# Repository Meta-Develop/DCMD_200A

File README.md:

# DCMD_200A

This repository is about the motor-driver for driving DC-brush motors on robots.

## License

This hardware design is licensed under [CERN-OHL-S-2.0](LICENSE). See [NOTICE](NOTICE) for attribution and third-party exceptions.

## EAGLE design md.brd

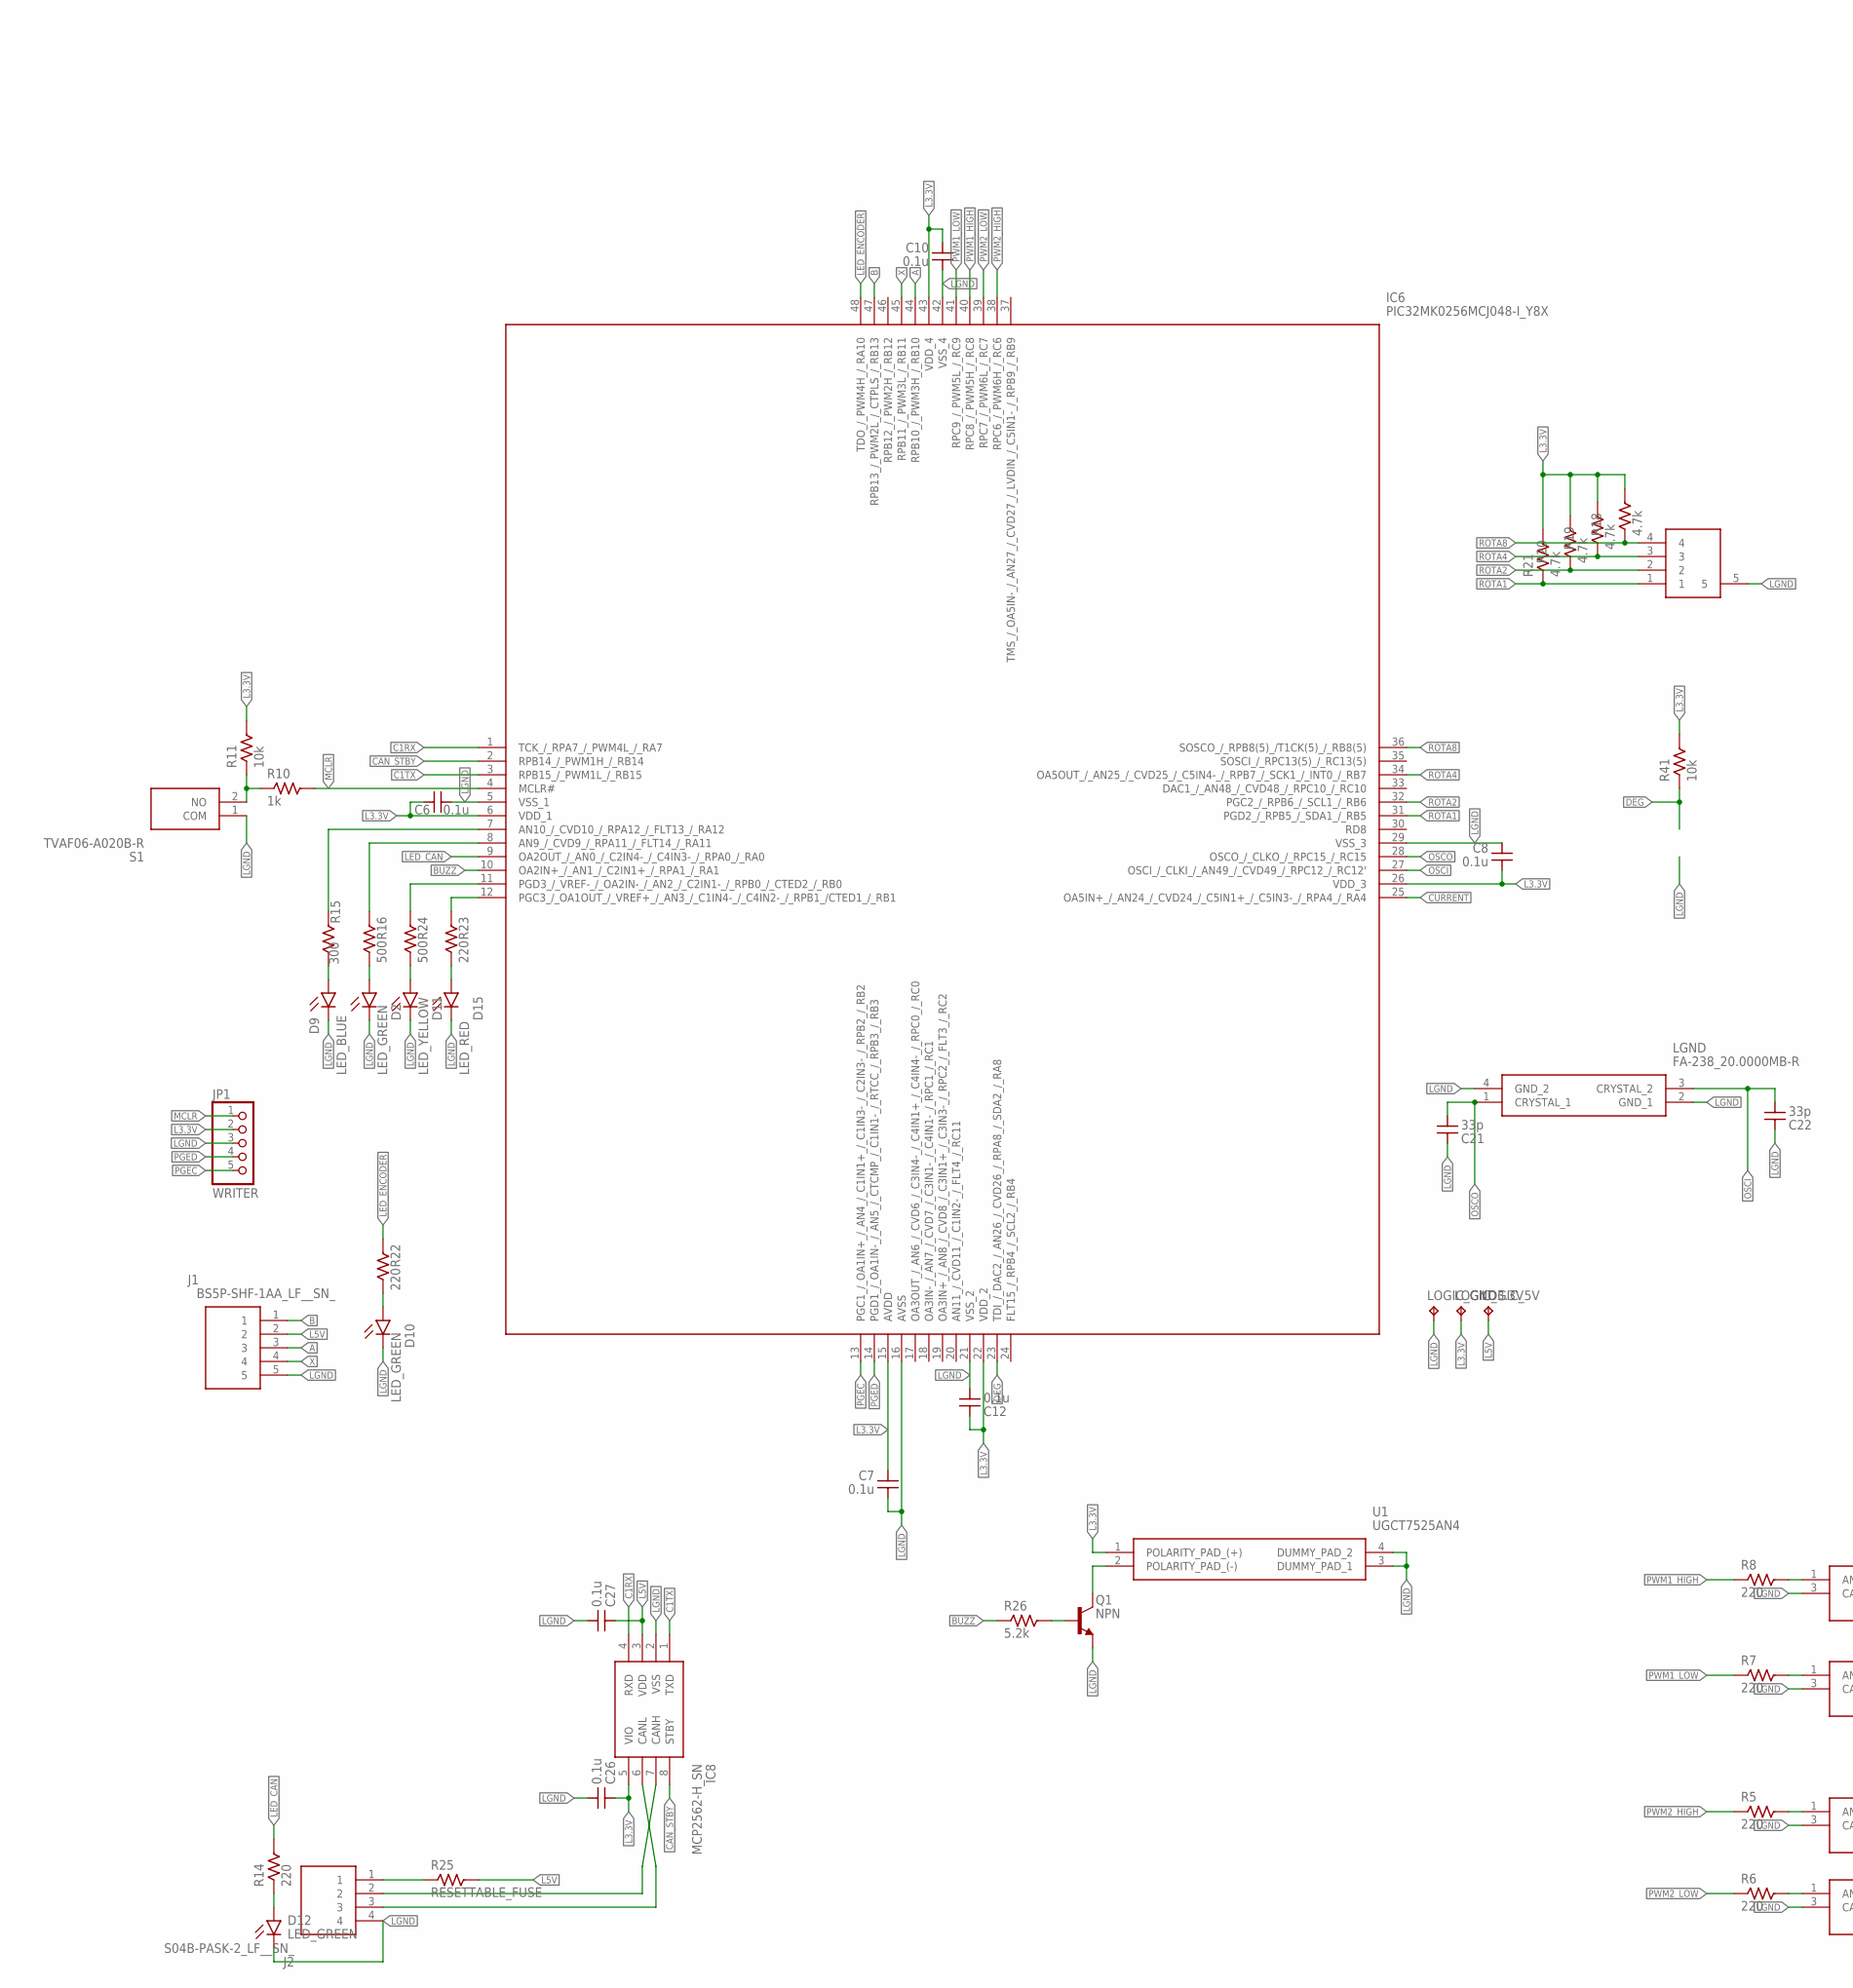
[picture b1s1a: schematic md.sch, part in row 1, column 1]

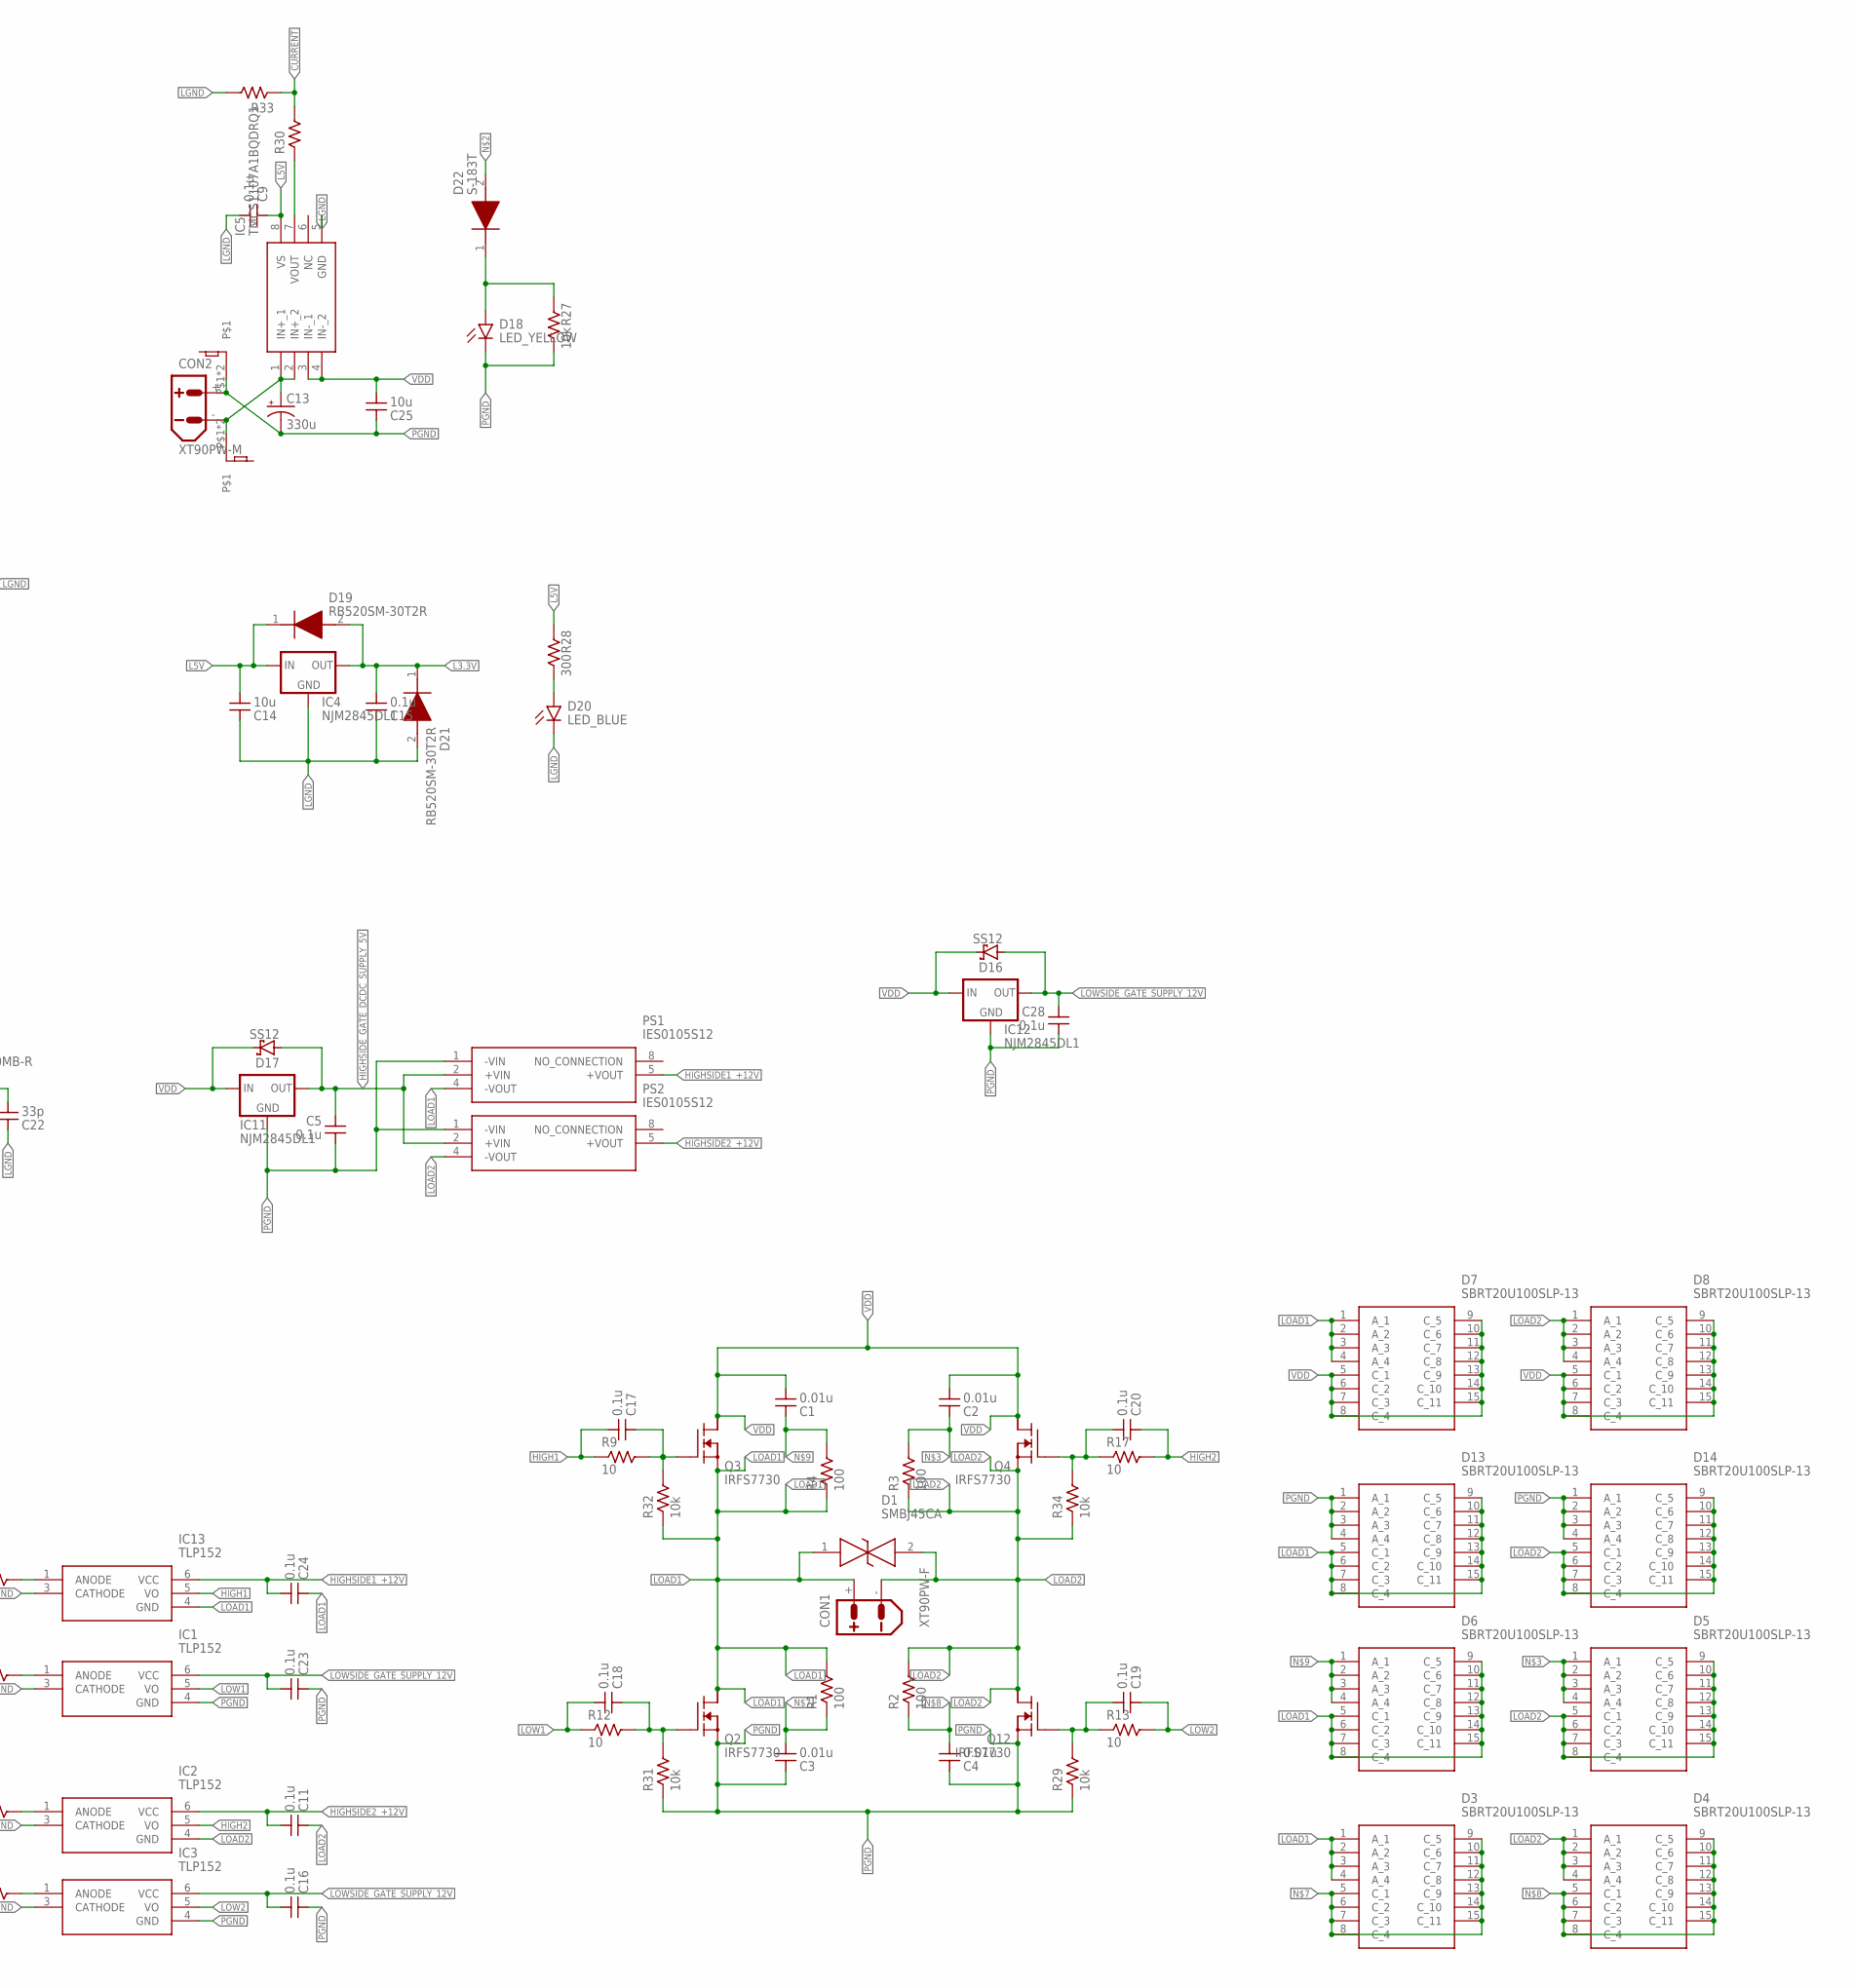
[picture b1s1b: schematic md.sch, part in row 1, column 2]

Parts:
C1, C2, C3, C4: 0.01u; C3216
C5, C6, C7, C8, C9, C10, C11, C12, C15, C16, C17, C18, C19, C20, C23, C24, C26, C27, C28: 0.1u; C1608
C13: 330u; CAPAE830X1050N
C14: 10u; C1608
C21, C22: 33p; C1608
C25: 10u; C3216
CON1: XT90PW-F
CON2: XT90PW-M
D1: SMBJ45CA; DIOM5336X265N
D2, D10, D12: LED_GREEN; LEDC1608X55N_FLAT-G
D3, D4, D5, D6, D7, D8, D13, D14: SBRT20U100SLP-13; SBRT20U100SLP13
D9, D20: LED_BLUE; LEDC1608X55N_FLAT-B
D11, D18: LED_YELLOW; LEDC1608X55N_FLAT-Y
D15: LED_RED; LEDC1608X55N_FLAT-R
D16, D17: SS12; SMA
D19, D21: RB520SM-30T2R; DIOC1608X70N
D22: S-183T; SODFL3516X70N
IC1, IC2, IC3, IC13: TLP152; 11-4L1S(5-PIN-SOIC)
IC4, IC11, IC12: NJM2845DL1; TO252
IC5: TMCS1107A1BQDRQ1; SOIC127P600X175-8N
IC6: PIC32MK0256MCJ048-I_Y8X; QFP50P900X900X120-48N
IC8: MCP2562-H_SN; SOIC127P600X175-8N
J1: BS5P-SHF-1AA_LF__SN_; HDRRA5W64P0X250_1X5_1250X600X5
J2: S04B-PASK-2_LF__SN_; S04BPASK2LFSN
JP1: WRITER; 1X05/90
LGND: FA-238_20.0000MB-R; FA238200000MBR
LOGIC_3.3V, LOGIC_5V: TPPAD1-13; P1-13
LOGIC_GND: TPPAD1-13; P1-13
PS1, PS2: IES0105S12
Q1: NPN; SC59
Q2, Q3, Q4, Q12: IRFS7730; D2PAK-7
R1, R2, R3, R4: 100; C2512
R5, R6, R7, R8, R14, R22, R23: 220; C1608
R9, R12, R13, R17: 10; 2010
R10: 1k; C1608
R11, R27, R29, R31, R32, R34, R41: 10k; C1608
R15, R28: 300; C1608
R16, R24: 500; C1608
R18, R19, R20, R21: 4.7k; C1608
R25: RESETTABLE_FUSE; C3216
R26: 5.2k; C1608
R30, R33: R1/10W; C1608
S1: TVAF06-A020B-R; TVAF06A020BR
S2: DRR4016
SCREW1, SCREW2: KIBANNNEZI; ＰＣＢ－５４Ｌ（Ｍ３）
U1: UGCT7525AN4

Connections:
A: IC6.44 (RPB10_/_PWM3H_/_RB10), J1.3
B: IC6.47 (RPB13_/_PWM2L_/_CTPLS_/_RB13), J1.1
BUZZ: IC6.10 (OA2IN+_/_AN1_/_C2IN1+_/_RPA1_/_RA1), R26.1
C1RX: IC6.1 (TCK_/_RPA7_/_PWM4L_/_RA7), IC8.4 (RXD)
C1TX: IC6.3 (RPB15_/_PWM1L_/_RB15), IC8.1 (TXD)
CAN_STBY: IC6.2 (RPB14_/_PWM1H_/_RB14), IC8.8 (STBY)
CURRENT: IC6.25 (OA5IN+_/_AN24_/_CVD24_/_C5IN1+_/_C5IN3-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), R30.2, R33.1
DEG: IC6.23 (TDI_/_DAC2_/_AN26_/_CVD26_/_RPA8_/_SDA2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), R41.1
H1GATE: C17.2, Q3.G (Nｃｈ-G), R9.P$2, R32.2
H2GATE: C20.1, Q4.G (Nｃｈ-G), R17.P$1, R34.2
HIGH1: C17.1, IC13.5 (VO), R9.P$1
HIGH2: C20.2, IC2.5 (VO), R17.P$2
HIGHSIDE1_+12V: C24.1, IC13.6 (VCC), PS1.5 (+VOUT)
HIGHSIDE2_+12V: C11.1, IC2.6 (VCC), PS2.5 (+VOUT)
HIGHSIDE_GATE_DCDC_SUPPLY_5V: C5.2, D17.A, IC11.3 (OUT), PS1.2 (+VIN), PS2.2 (+VIN)
IN1: IC8.7 (CANH), J2.2
IN2: IC8.6 (CANL), J2.3
L1GATE: C18.2, Q2.G (Nｃｈ-G), R12.P$2, R31.2
L2GATE: C19.1, Q12.G (Nｃｈ-G), R13.P$1, R29.2
L3.3V: C6.2, C7.2, C8.1, C10.2, C12.2, C15.1, C26.2, D19.2 (A), D21.1 (K), IC4.3 (OUT), IC6.6 (VDD_1), IC6.15 (AVDD), IC6.22 (VDD_2), IC6.26 (VDD_3), IC6.43 (VDD_4), IC8.5 (VIO), JP1.2, LOGIC_3.3V.TP, R11.2, R18.2, R19.2, R20.2, R21.2, R41.2, U1.1 (POLARITY_PAD_(+))
L5V: C9.2, C14.1, C27.2, D19.1 (K), IC4.1 (IN), IC5.8 (VS), IC8.3 (VDD), J1.2, LOGIC_5V.TP, R25.2, R28.2
LED_CAN: IC6.9 (OA2OUT_/_AN0_/_C2IN4-_/_C4IN3-_/_RPA0_/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), R14.2
LED_ENCODER: IC6.48 (TDO_/_PWM4H_/_RA10), R22.2
LGND: C6.1, C7.1, C8.2, C9.1, C10.1, C12.1, C14.2, C15.2, C21.2, C22.2, C26.1, C27.1, D2.C, D9.C, D10.C, D11.C, D12.C, D15.C, D20.C, D21.2 (A), IC1.3 (CATHODE), IC2.3 (CATHODE), IC3.3 (CATHODE), IC4.2 (GND), IC5.5 (GND), IC6.5 (VSS_1), IC6.16 (AVSS), IC6.21 (VSS_2), IC6.29 (VSS_3), IC6.42 (VSS_4), IC8.2 (VSS), IC13.3 (CATHODE), J1.5, J2.4, JP1.3, LGND.2 (GND_1), LGND.4 (GND_2), LOGIC_GND.TP, Q1.E, R33.2, S1.1 (COM), S2.5, U1.3 (DUMMY_PAD_1), U1.4 (DUMMY_PAD_2)
LOAD1: C24.2, CON1.+, D1.1, D3.1 (A_1), D3.2 (A_2), D3.3 (A_3), D3.4 (A_4), D6.5 (C_1), D6.6 (C_2), D6.7 (C_3), D6.8 (C_4), D6.9 (C_5), D6.10 (C_6), D6.11 (C_7), D6.12 (C_8), D6.13 (C_9), D6.14 (C_10), D6.15 (C_11), D7.1 (A_1), D7.2 (A_2), D7.3 (A_3), D7.4 (A_4), D13.5 (C_1), D13.6 (C_2), D13.7 (C_3), D13.8 (C_4), D13.9 (C_5), D13.10 (C_6), D13.11 (C_7), D13.12 (C_8), D13.13 (C_9), D13.14 (C_10), D13.15 (C_11), IC13.4 (GND), PS1.4 (-VOUT), Q2.D (NｃｈD), Q3.S1 (NｃｈS), Q3.S2 (NｃｈS), Q3.S3 (NｃｈS), Q3.S4 (NｃｈS), Q3.S5 (NｃｈS), R1.2, R4.1, R32.1
LOAD2: C11.2, CON1.-, D1.2, D4.1 (A_1), D4.2 (A_2), D4.3 (A_3), D4.4 (A_4), D5.5 (C_1), D5.6 (C_2), D5.7 (C_3), D5.8 (C_4), D5.9 (C_5), D5.10 (C_6), D5.11 (C_7), D5.12 (C_8), D5.13 (C_9), D5.14 (C_10), D5.15 (C_11), D8.1 (A_1), D8.2 (A_2), D8.3 (A_3), D8.4 (A_4), D14.5 (C_1), D14.6 (C_2), D14.7 (C_3), D14.8 (C_4), D14.9 (C_5), D14.10 (C_6), D14.11 (C_7), D14.12 (C_8), D14.13 (C_9), D14.14 (C_10), D14.15 (C_11), IC2.4 (GND), PS2.4 (-VOUT), Q4.S1 (NｃｈS), Q4.S2 (NｃｈS), Q4.S3 (NｃｈS), Q4.S4 (NｃｈS), Q4.S5 (NｃｈS), Q12.D (NｃｈD), R2.2, R3.1, R34.1
LOW1: C18.1, IC1.5 (VO), R12.P$1
LOW2: C19.2, IC3.5 (VO), R13.P$2
LOWSIDE_GATE_SUPPLY_12V: C16.1, C23.1, C28.2, D16.A, IC1.6 (VCC), IC3.6 (VCC), IC12.3 (OUT)
MCLR: IC6.4 (MCLR#), JP1.1, R10.2
unnamed: D10.A, R22.1
unnamed: C13.1 (+), CON2.-, D22.2 (A), IC5.1 (IN+_1), IC5.2 (IN+_2), SCREW1.P$1, SCREW1.P$2
unnamed: C2.2, D5.1 (A_1), D5.2 (A_2), D5.3 (A_3), D5.4 (A_4), R3.2
unnamed: IC3.1 (ANODE), R6.2
unnamed: R10.1, R11.1, S1.2 (NO)
unnamed: IC6.7 (AN10_/_CVD10_/_RPA12_/_FLT13_/_RA12), R15.2
unnamed: C3.1, D3.5 (C_1), D3.6 (C_2), D3.7 (C_3), D3.8 (C_4), D3.9 (C_5), D3.10 (C_6), D3.11 (C_7), D3.12 (C_8), D3.13 (C_9), D3.14 (C_10), D3.15 (C_11), R1.1
unnamed: C4.1, D4.5 (C_1), D4.6 (C_2), D4.7 (C_3), D4.8 (C_4), D4.9 (C_5), D4.10 (C_6), D4.11 (C_7), D4.12 (C_8), D4.13 (C_9), D4.14 (C_10), D4.15 (C_11), R2.1
unnamed: C1.2, D6.1 (A_1), D6.2 (A_2), D6.3 (A_3), D6.4 (A_4), R4.2
unnamed: IC6.8 (AN9_/_CVD9_/_RPA11_/_FLT14_/_RA11), R16.2
unnamed: D9.A, R15.1
unnamed: D2.A, R16.1
unnamed: IC6.11 (PGD3_/_VREF-_/_OA2IN-_/_AN2_/_C2IN1-_/_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), R24.2
unnamed: IC2.1 (ANODE), R5.2
unnamed: IC6.12 (PGC3_/_OA1OUT_/_VREF+_/_AN3_/_C1IN4-_/_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), R23.2
unnamed: D11.A, R24.1
unnamed: D15.A, R23.1
unnamed: J2.1, R25.1
unnamed: D12.A, R14.1
unnamed: D18.A, D22.1 (K), R27.2
unnamed: D20.A, R28.1
unnamed: IC5.7 (VOUT), R30.1
unnamed: Q1.C, U1.2 (POLARITY_PAD_(-))
unnamed: Q1.B, R26.2
unnamed: IC1.1 (ANODE), R7.2
unnamed: IC13.1 (ANODE), R8.2
OSCI: C22.1, IC6.27 (OSCI_/_CLKI_/_AN49_/_CVD49_/_RPC12_/_RC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), LGND.3 (CRYSTAL_2)
OSCO: C21.1, IC6.28 (OSCO_/_CLKO_/_RPC15_/_RC15), LGND.1 (CRYSTAL_1)
PGEC: IC6.13 (PGC1_/_OA1IN+_/_AN4_/_C1IN1+_/_C1IN3-_/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), JP1.5
PGED: IC6.14 (PGD1_/_OA1IN-_/_AN5_/_CTCMP_/_C1IN1-_/_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), JP1.4
PGND: C3.2, C4.2, C5.1, C13.2 (-), C16.2, C23.2, C25.2, C28.1, CON2.+, D13.1 (A_1), D13.2 (A_2), D13.3 (A_3), D13.4 (A_4), D14.1 (A_1), D14.2 (A_2), D14.3 (A_3), D14.4 (A_4), D18.C, IC1.4 (GND), IC3.4 (GND), IC11.2 (GND), IC12.2 (GND), PS1.1 (-VIN), PS2.1 (-VIN), Q2.S1 (NｃｈS), Q2.S2 (NｃｈS), Q2.S3 (NｃｈS), Q2.S4 (NｃｈS), Q2.S5 (NｃｈS), Q12.S1 (NｃｈS), Q12.S2 (NｃｈS), Q12.S3 (NｃｈS), Q12.S4 (NｃｈS), Q12.S5 (NｃｈS), R27.1, R29.1, R31.1, SCREW2.P$1, SCREW2.P$2
PWM1_HIGH: IC6.40 (RPC8_/_PWM5H_/_RC8), R8.1
PWM1_LOW: IC6.41 (RPC9_/_PWM5L_/_RC9), R7.1
PWM2_HIGH: IC6.38 (RPC6_/_PWM6H_/_RC6), R5.1
PWM2_LOW: IC6.39 (RPC7_/_PWM6L_/_RC7), R6.1
ROTA1: IC6.31 (PGD2_/_RPB5_/_SDA1_/_RB5), R21.1, S2.1
ROTA2: IC6.32 (PGC2_/_RPB6_/_SCL1_/_RB6), R20.1, S2.2
ROTA4: IC6.34 (OA5OUT_/_AN25_/_CVD25_/_C5IN4-_/_RPB7_/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), R19.1, S2.3
ROTA8: IC6.36 (SOSCO_/_RPB8(5)_/T1CK(5)_/_RB8(5)), R18.1, S2.4
VDD: C1.1, C2.1, C25.1, D7.5 (C_1), D7.6 (C_2), D7.7 (C_3), D7.8 (C_4), D7.9 (C_5), D7.10 (C_6), D7.11 (C_7), D7.12 (C_8), D7.13 (C_9), D7.14 (C_10), D7.15 (C_11), D8.5 (C_1), D8.6 (C_2), D8.7 (C_3), D8.8 (C_4), D8.9 (C_5), D8.10 (C_6), D8.11 (C_7), D8.12 (C_8), D8.13 (C_9), D8.14 (C_10), D8.15 (C_11), D16.C, D17.C, IC5.3 (IN-_1), IC5.4 (IN-_2), IC11.1 (IN), IC12.1 (IN), Q3.D (NｃｈD), Q4.D (NｃｈD)
X: IC6.45 (RPB11_/_PWM3L_/_RB11), J1.4

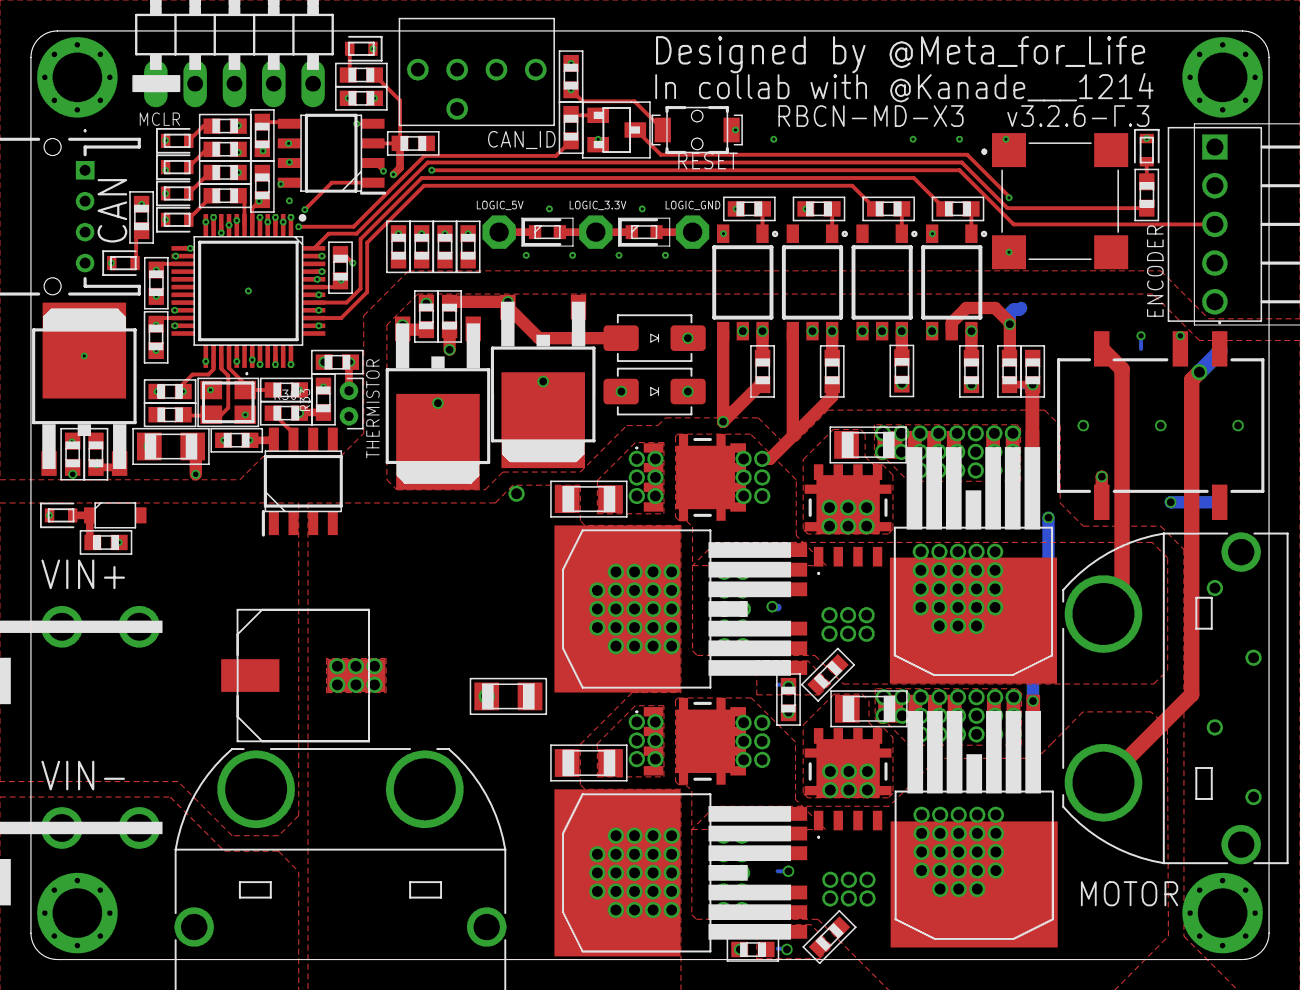
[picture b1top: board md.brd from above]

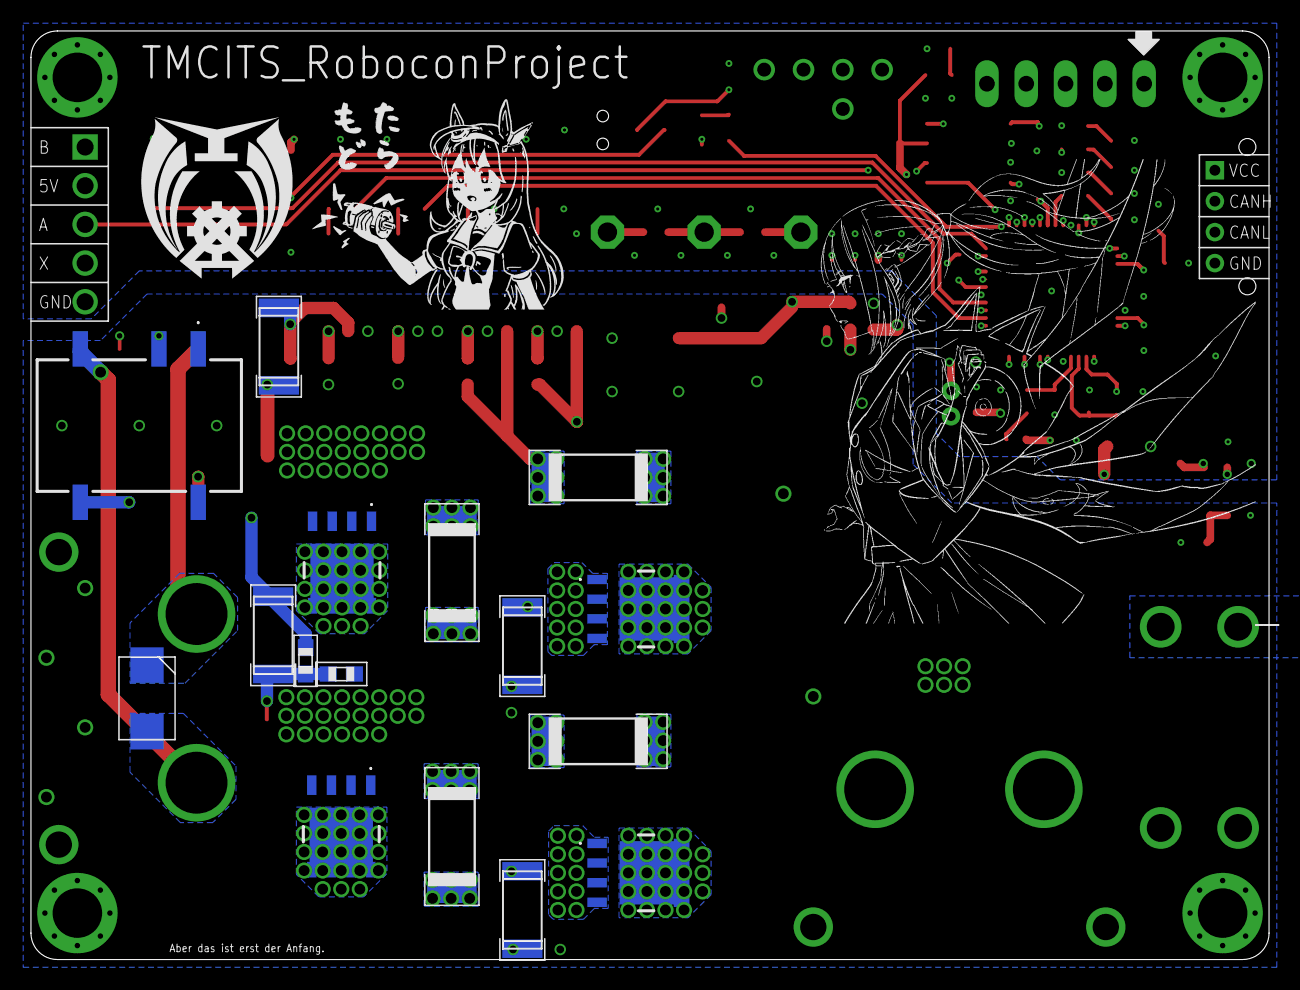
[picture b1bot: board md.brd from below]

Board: 4 copper layers, 80.0 x 60.0 mm, 117 parts (17 on the bottom side), 71 nets.

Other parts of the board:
U$1: LOGO

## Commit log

2024-09-03 added brd & sch
2024-09-03 Update LICENSE
2024-09-03 changed file directory
